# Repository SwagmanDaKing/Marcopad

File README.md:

# Marcopad
My Hack Club Marcopad Repository
This is my Submission for the Hack Club Macropad. Isnt it pretty...

Here is how the case with everything is supossed to look in the end

This was my first time using Fusion, KiCad, or GitHub so if its not good please understand. It was fun espexcially using KiCad do design and wire the PCB.
This is something i want to do in my future so it helps to have a website like this to give a first intruduction
Here is my updated circuit diagramm... now with a rotary encoder ment for controlling volume

Challanges:
not knowing how to code, or having used any CAD or design tools before was tough.
didnt help.
but the tutorial was straight foreward enough.
i hope i did the freestyle parts (3d modles in the cad and wireing) right
this was my first time designing anything and it like to get feedback.

Specifications

BOM:
4x Cherry MX Switches

2x SK6812 MINI Leds

1x XIAO RP2040

4x Blank DSA Keycaps

4x M3x16 Bolt

4x M3 Heatset

1x EC11 Rotary Encoder Switch Vertical_H20mm

Others:

KMK Firmware
Top Case.stl
Bottom Case.stl

(P.S i hope ts all right)

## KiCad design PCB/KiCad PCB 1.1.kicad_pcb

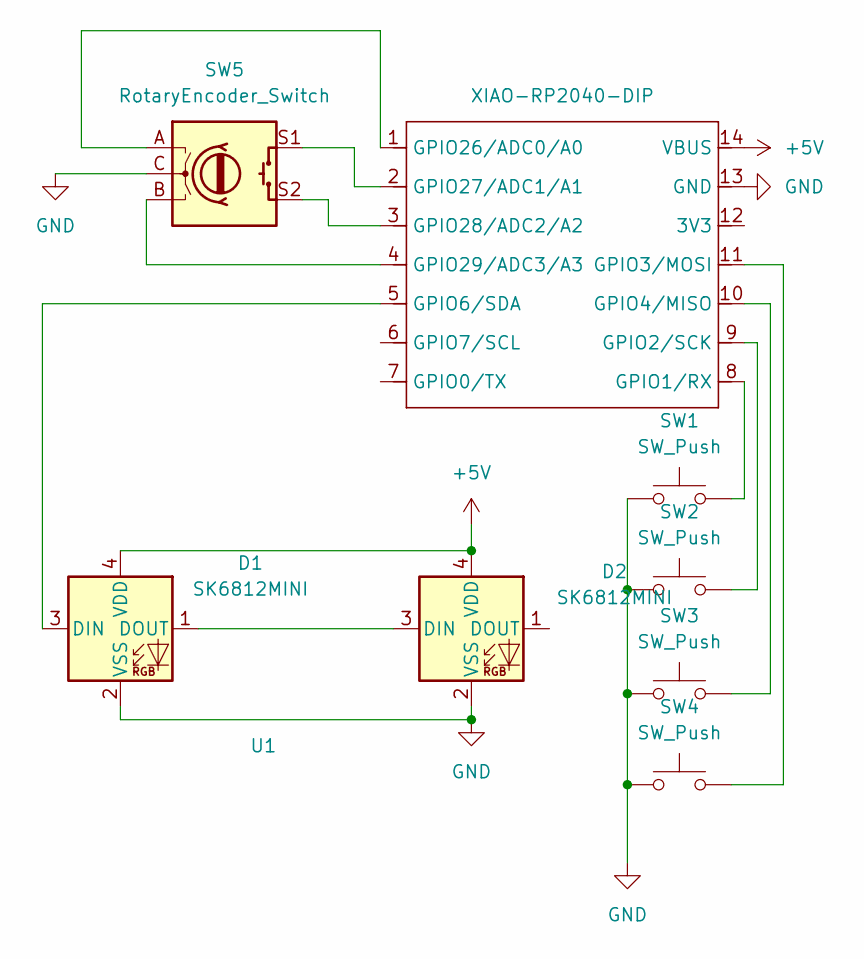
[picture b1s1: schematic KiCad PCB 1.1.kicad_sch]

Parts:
D1, D2: SK6812MINI; LED_SK6812MINI_PLCC4_3.5x3.5mm_P1.75mm
SW1, SW2, SW3, SW4: SW_Push; SW_Cherry_MX_1.00u_PCB
SW5: RotaryEncoder_Switch; RotaryEncoder_Alps_EC11E-Switch_Vertical_H20mm
U1: XIAO-RP2040-DIP

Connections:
+5V: D1.4 (VDD), D2.4 (VDD), U1.14 (VBUS)
GND: D1.2 (VSS), D2.2 (VSS), SW1.1, SW2.1, SW3.1, SW4.1, SW5.C, U1.13 (GND)
unnamed: D1.3 (DIN), U1.5 (GPIO6/SDA)
unnamed: D1.1 (DOUT), D2.3 (DIN)
unnamed: SW1.2, U1.8 (GPIO1/RX)
unnamed: SW2.2, U1.9 (GPIO2/SCK)
unnamed: SW4.2, U1.11 (GPIO3/MOSI)
unnamed: SW3.2, U1.10 (GPIO4/MISO)
unnamed: SW5.A, U1.1 (GPIO26/ADC0/A0)
unnamed: SW5.S1, U1.2 (GPIO27/ADC1/A1)
unnamed: SW5.S2, U1.3 (GPIO28/ADC2/A2)
unnamed: SW5.B, U1.4 (GPIO29/ADC3/A3)

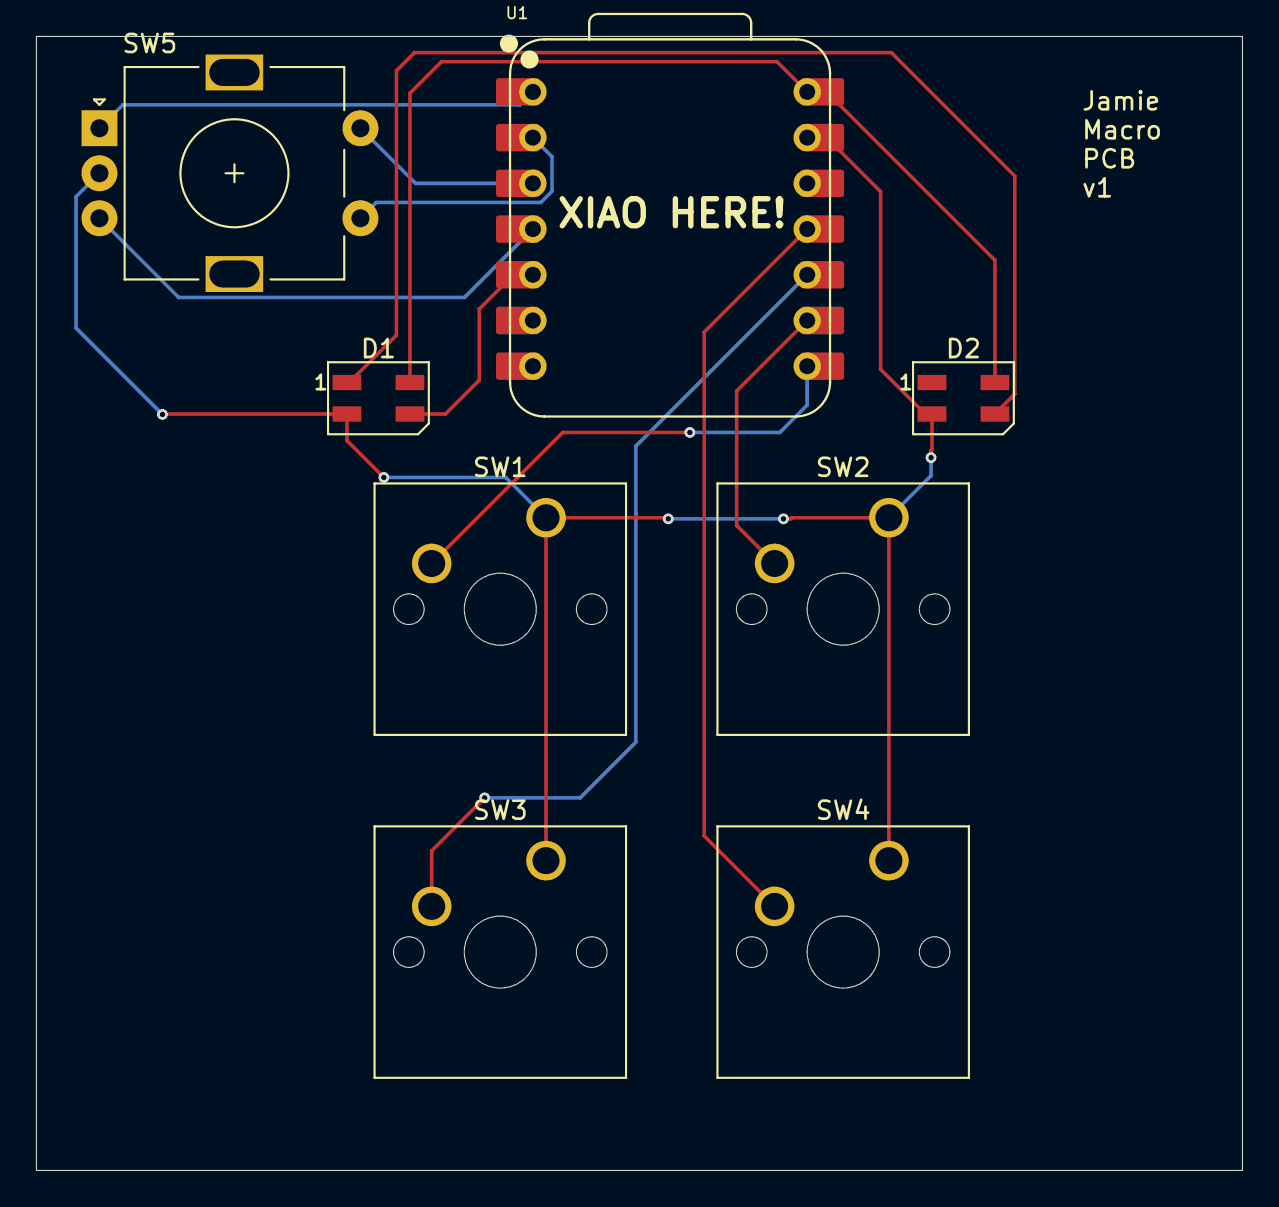
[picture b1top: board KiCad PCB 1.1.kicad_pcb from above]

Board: 2 copper layers, 67.0 x 63.0 mm, 8 parts (0 on the bottom side), 12 nets.

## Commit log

2025-12-22 Create tf how dui you do foilders
2025-12-22 Create folder
